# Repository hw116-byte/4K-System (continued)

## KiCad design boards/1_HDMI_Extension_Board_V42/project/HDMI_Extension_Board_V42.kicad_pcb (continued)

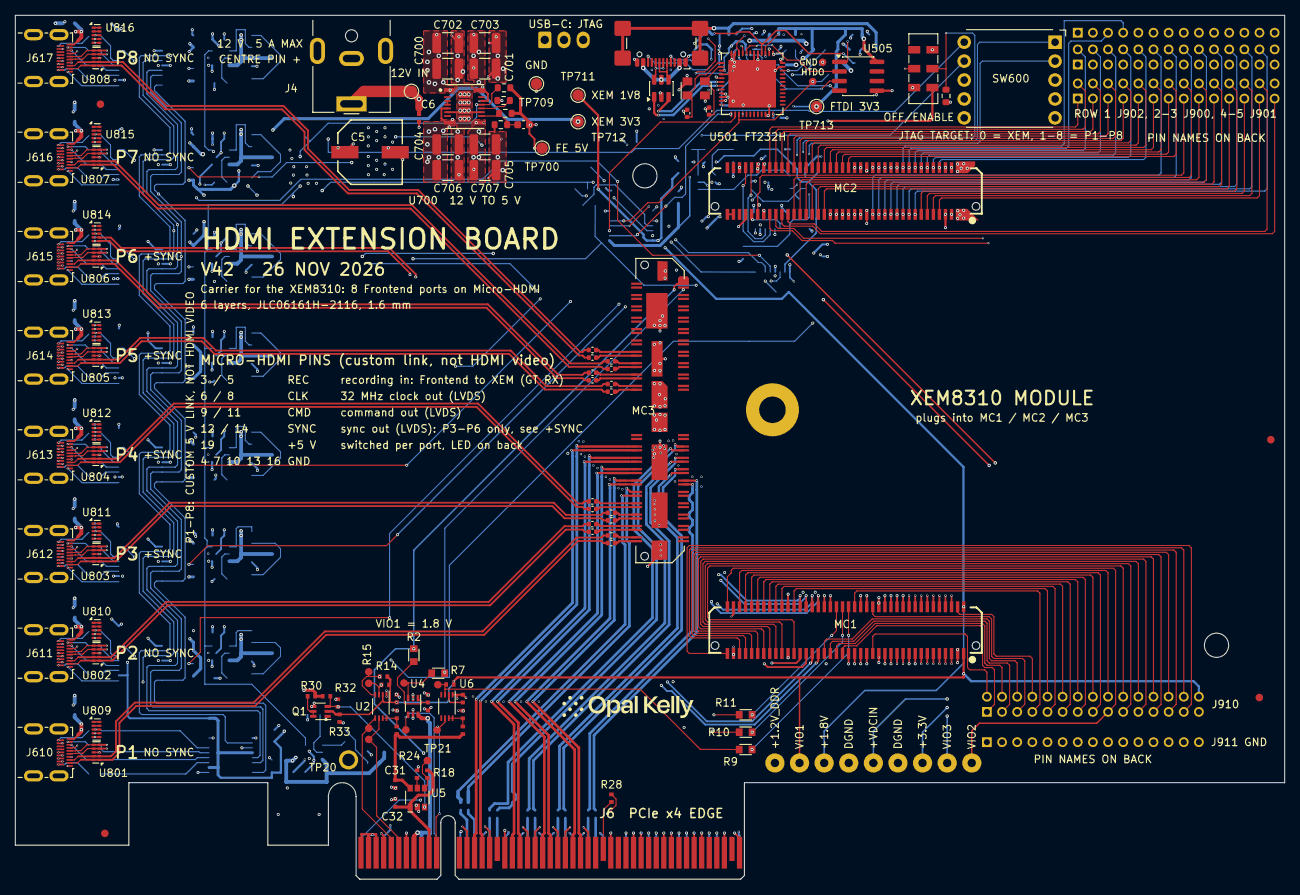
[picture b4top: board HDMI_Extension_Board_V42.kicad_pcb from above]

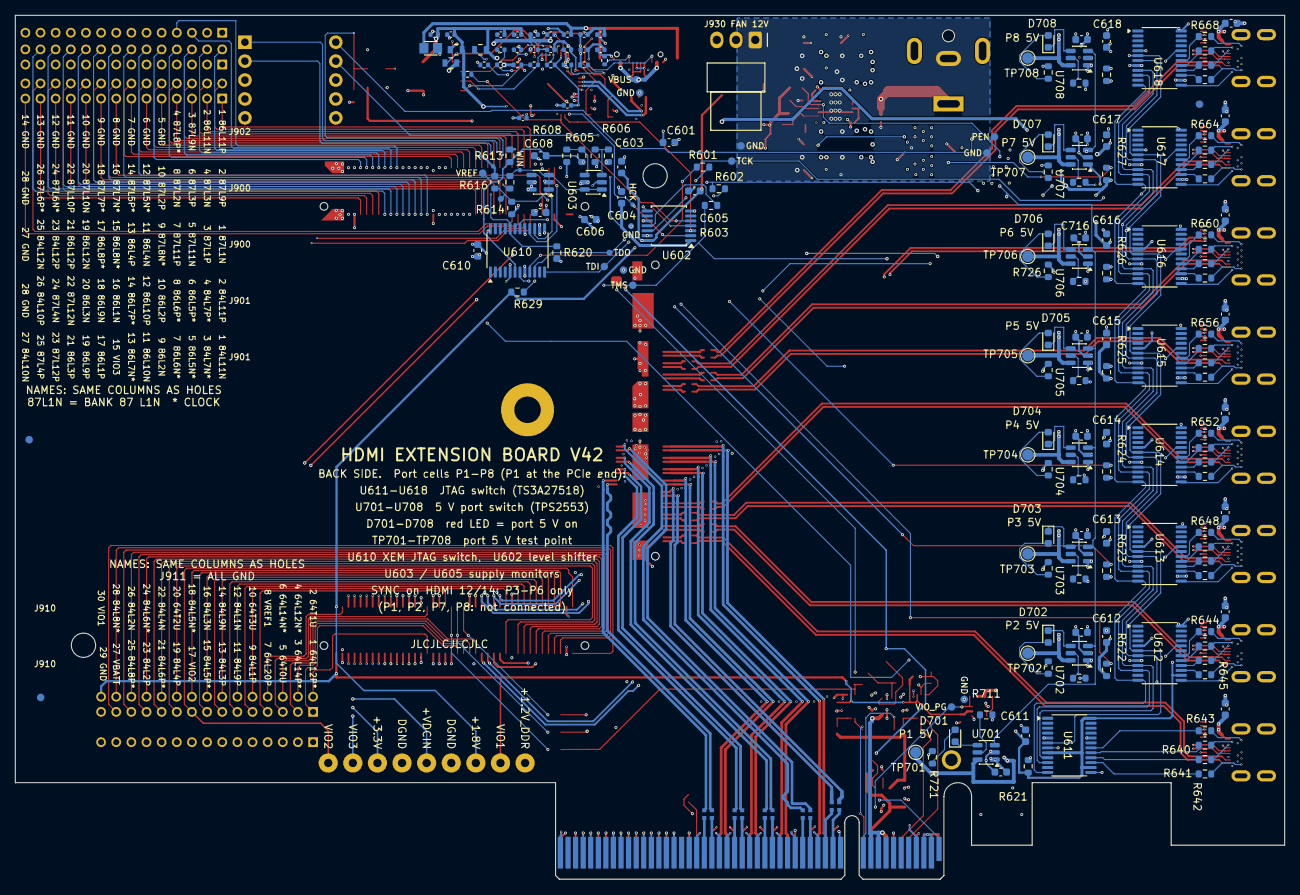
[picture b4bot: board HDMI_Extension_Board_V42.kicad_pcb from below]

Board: 6 copper layers, 167.6 x 114.1 mm, 340 parts (200 on the bottom side), 388 nets.

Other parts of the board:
*: Opal Kelly Logo; BRK_Logo_c689e08d
FID1, FID5, FID6, FID7: FIDUCIAL; BRK_FID1
FID2: FIDUCIAL; BRK_FID2
FID3: FIDUCIAL; BRK_FID3
FID4: FIDUCIAL; BRK_FID4
MH2, MH3: Standoff M3; Standoff_Hole_3.2mm_NPTH

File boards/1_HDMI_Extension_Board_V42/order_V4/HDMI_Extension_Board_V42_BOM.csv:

Comment,Designator,Footprint,JLCPCB Part #
CL05B104KO5NNNC (100nF 10% 16V X7R 0402),"C7,C8,C9,C10,C11,C12,C27,C28,C31,C32,C501,C502,C505,C508,C509,C510,C511,C514,C516,C517,C518",BRK8310_C10,C1525
CL05B224KO5NNNC (220nF 10% 16V X7R 0402),"C13,C14,C15,C16,C17,C18,C19,C20",BRK8310_C13,C16772
EEE-FK1E221GP,C5,BRK_C5,C401715
4.7u,C500,C500,C342983
18p,"C503,C504",C504,C22442494
100n,C506,C506,C1525
4.7u,"C507,C512,C513,C515",C515,C87147
10n,C519,C519,C2649513
CL05B104KB54PNC (100nF 10% 50V X7R 0402),C6,BRK_C6,C307331
2.2u,"C601,C603",C_0603_1608Metric,C100082
100nF,"C604,C605,C606,C609,C610,C611,C612,C613,C614,C615,C616,C617,C618,C711,C712,C713,C714,C715,C716,C717,C718",C_0603_1608Metric,C14663
1n,C608,C_0603_1608Metric,C8808
10uF,"C700,C701,C702,C703",C_1210_3225Metric,C77102
47uF,"C704,C705,C706,C707",C_1210_3225Metric,C77101
22pF,C708,C_0603_1608Metric,C376775
USBLC6-2SC6,D500,D500,C7519
RED,"D701,D702,D703,D704,D705,D706,D707,D708",LED_0603_1608Metric,C94869
600R,"FB500,FB501,FB502",FB502,C19330
220R @100MHz,FB503,FB503,C76818
PJ-063AH,J4,BarrelJack_CUI_PJ-063AH_Horizontal,C22434582
USB4110-GF-A,J500,J500,C5143397
467651001,"J610,J611,J612,J613,J614,J615,J616,J617",HDMI_Micro-D_Molex_46765-1xxx,C563878
YXY-PZ2.0-2X14PIN-DIP,"J900,J901",PinHeader_2x14_P2.00mm_V41,C56596886
YXY-PZ2.0-1X14PIN-DIP,J902,PinHeader_1x14_P2.00mm_V41,C56596719
YXY-PZ2.0-2X15PIN-DIP,J910,PinHeader_2x15_P2.00mm_V41,C56596887
YXY-PZ2.0-1X15PIN-DIP,J911,PinHeader_1x15_P2.00mm_V41,C56596720
PZ254V-11-01P,"J920,J921,J922,J923,J924,J925,J926,J927,J928",PinHeader_1x01_P2.54mm_Pad2.54_D1.1_V41,C492400
22-05-3031,J930,Molex_KK-254_22-05-3031_1x03_P2.54mm_Horizontal,C505040
BTE-040-01-F-D-A,"MC1,MC2",BRK_MC1,C2914307
QTH-040-01-F-D-DP-A,MC3,BRK_MC3,C7330812
SI1922EDH-T1-GE3,Q1,BRK8310_Q1,C141538
CRCW06030000Z0EA,"R2,R7,R9,R10,R11",BRK8310_R10,C844915
CRCW0402200KFKED,"R13,R23",BRK8310_R13,C482093
CRCW04024K75FKED,"R14,R15,R30,R31",BRK8310_R14,C844510
CRCW0402100KFKED,"R18,R24,R25,R32,R33,R502,R503",BRK8310_R18,C481918
CRCW04020000Z0ED,R28,BRK8310_R28,C190119
5.1k 1%,"R500,R501",R501,C2076825
2k,R504,R504,C482125
10k,"R505,R506,R509",R509,C71617
12k 1%,R507,R507,C481938
3.3k,"R600,R721,R722,R723,R724,R725,R726,R727,R728",R_0603_1608Metric,C22978
22R,"R601,R602,R603",R_0603_1608Metric,C23345
301k,R605,R_0603_1608Metric,C23026
100k,"R606,R608,R616",R_0603_1608Metric,C25803
402k,R607,R_0603_1608Metric,C23048
68k,R613,R_0603_1608Metric,C23231
4.7k,R614,R_0603_1608Metric,C23162
12k,R615,R_0603_1608Metric,C22790
10k,"R620,R621,R622,R623,R624,R625,R626,R627,R628",R_0603_1608Metric,C25804
1k,R629,R_0603_1608Metric,C21190
100R,"R640,R641,R642,R643,R644,R645,R646,R647,R648,R649,R650,R651,R652,R653,R654,R655,R656,R657,R658,R659,R660,R661,R662,R663,R664,R665,R666,R667,R668,R669,R670,R671",R_0603_1608Metric,C22775
40.2k,R700,R_0603_1608Metric,C137723
10k,"R701,R703",R_0603_1608Metric,C98220
13k,R702,R_0603_1608Metric,C22797
37.4k,"R711,R712,R713,R714,R715,R716,R717,R718",R_0603_1608Metric,C227846
SRBQ490100,SW600,ALPS_SRBQ490100_1P9T,C370985
JS202011JCQN,SW601,SW700,C221665
PCA9306DCUR,"U2,U6",BRK8310_U2,C33196
SN74AXC1T45DCK,U4,BRK8310_U4,C2677392
AP22653AW6-7,U5,BRK8310_U5,C1511768
FT232HQ-REEL,U501,U501,C82158
93LC56BT-I/SN,U505,SOIC-8_3.9x4.9mm_P1.27mm,C6164
TXU0304PWR,U602,TSSOP-14_4.4x5mm_P0.65mm,C4364118
TPS3700DDCR,U603,SOT-23-6,C33002
TPS3808G30DBVR,U605,SOT-23-6,C189211
TS3A27518EPWR,"U610,U611,U612,U613,U614,U615,U616,U617,U618",TSSOP-24_4.4x7.8mm_P0.65mm,C443721
TPSM63606RDLR,U700,TI_TPSM63606_RDL0020A_EVM,C5219325
TPS2553DBVR,"U701,U702,U703,U704,U705,U706,U707,U708",SOT-23-6,C55266
TPD4E02B04DQAR,"U801,U802,U803,U804,U805,U806,U807,U808,U809,U810,U811,U812,U813,U814,U815,U816",USON-10_2.5x1.0mm_P0.5mm,C106794
7U12000E18UCG 12MHz,Y500,Y500,C524717
CL10A105KB8NNNC (1uF 10% 50V X5R 0603),"C721,C722,C723,C724,C725,C726,C727,C728",C_0603_1608Metric,C15849
CL05B104KO5NNNC (100nF 10% 16V X7R 0402),"C745,C746,C747,C748,C749,C750,C751,C752,C753,C754,C755,C756,C757,C758,C759,C760",C_0402_1005Metric,C1525

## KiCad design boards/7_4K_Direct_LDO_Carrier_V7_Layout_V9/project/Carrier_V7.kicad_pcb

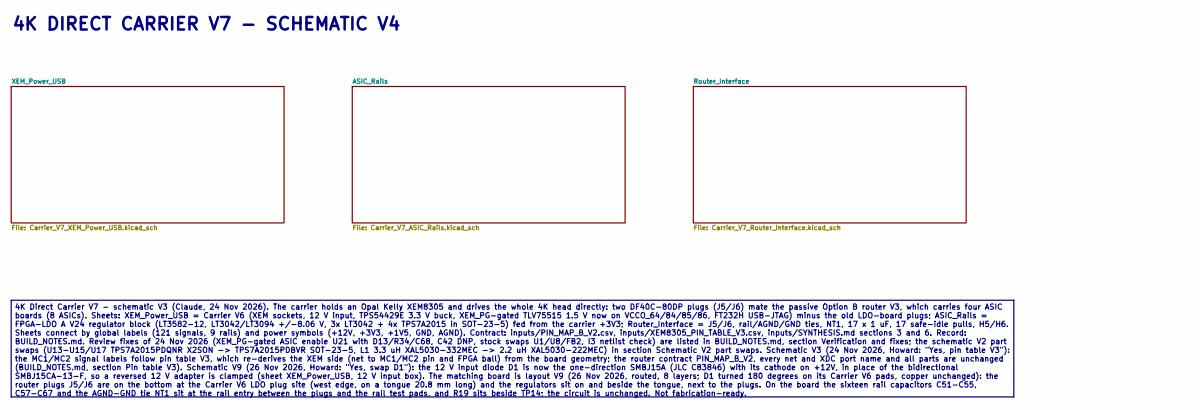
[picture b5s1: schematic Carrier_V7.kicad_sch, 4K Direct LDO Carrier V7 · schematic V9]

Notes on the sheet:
4K Direct Carrier V7 - schematic V3 (Claude, 24 Nov 2026). The carrier holds an Opal Kelly XEM8305 and drives the whole 4K head directly: two DF40C-80DP plugs (J5/J6) mate the passive Option B router V3, which carries four ASIC boards (8 ASICs). Sheets: XEM_Power_USB = Carrier V6 (XEM sockets, 12 V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
4K DIRECT CARRIER V7 - SCHEMATIC V4

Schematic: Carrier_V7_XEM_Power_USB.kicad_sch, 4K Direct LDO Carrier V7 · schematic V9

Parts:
C1: 0.1u 25v; C_0402_1005Metric; Voltage 25V; Tolerance 10%; MPN CL05B104KA5NNNC; LCSC C155422
C2: 220u 25v; CP_Panasonic_EEEFTE221XAL_D6.3x7.7_V3; MPN EEEFTE221XAL; LCSC C1881633
C3: 22u 35V; C_1206_3216Metric; Voltage 35V; Tolerance 20%; MPN C3216X5R1V226MTJ00E; LCSC C342620
C4: 0.1u 25V; C_0402_1005Metric; Voltage 25V; Tolerance 10%; MPN CL05B104KA5NNNC; LCSC C155422
C5: 1u 25V; C_0603_1608Metric; Voltage 25V; Tolerance 10%; MPN CL10A105KA8NNNC; LCSC C5673
C6: 3.3n 50V; C_0402_1005Metric; Voltage 50V; Tolerance 10%; MPN CL05B332KB5NNNC; LCSC C26404
C7: 0.1u 16V; C_0402_1005Metric; Voltage 16V; Tolerance 10%; MPN CL05B104KO5NNNC; LCSC C1525
C8, C9: 22u 10V; C_1206_3216Metric; Voltage 10V; Tolerance 10%; MPN CL31B226KPHNNNE; LCSC C87996
C10: 10p 50V; C_0402_1005Metric; Voltage 50V; Tolerance 5%; MPN CL05C100JB5NNNC; LCSC C32949
C11, C12: 4.7u 10V X5R; C_0402_1005Metric; MPN CL05A475MP5NRNC; LCSC C23733
C13: 4.7u; C_0402_1005Metric; Voltage 10V; MPN CL05A475MP5NRNC; LCSC C23733
C14, C16, C19, C22, C23, C24, C25, C28, C30, C31, C32, C34, C35, C36, C37, C38, C39, C40, C41, C70: 100n; C_0402_1005Metric; Voltage 16V; Tolerance 10%; MPN CL05B104KO5NNNC; LCSC C1525
C17, C18: 18p; C_0402_1005Metric; MPN C0402C180J5GACTU; LCSC C22442494
C20, C33: 10n; C_0402_1005Metric; Voltage 16V; Tolerance 10%; MPN C0402C103K4RACTU; LCSC C2649513
C21, C26, C27, C29: 4.7u; C_0402_1005Metric; Voltage 6.3V; Tolerance 20%; MPN JMK105BBJ475MV-F; LCSC C87147
C69: 4.7u; C_0402_1005Metric; MPN CL05A475MP5NRNC; LCSC C23733
D1: SMBJ15A; D_SMB; MPN SMBJ15A; LCSC C83846
D2: 598-8070-107F; LED_0603_1608Metric; MPN 5988070107F; LCSC C6695603
D3: APT1608LZGCK; LED_Kingbright_APT1608LZGCK_V2; Voltage 2.65V typ @2mA; MPN APT1608LZGCK; LCSC C5246833
D4: APT1608LSYCK/J3-PRV; LED_Kingbright_APT1608LSYCK_J3_PRV_V2; Voltage 1.85V typ @2mA; MPN APT1608LSYCK/J3-PRV; LCSC C5246836
FB1, FB3, FB4: 600R; Ferrite_Bead_Murata_BLM18KG601SN1D_0603_V4; MPN BLM18KG601SN1D; LCSC C85833
FB2: 220R @100MHz; BRK8305_A03_FB503; MANUFACTURER_PN BLM21PG221SH1D; LCSC C88994
H1, H2, H3, H4: XEM M3 NPTH; MountingHole_3.2mm_XEM_M3_Keepout
J3: PJ-102AH; PJ102AH; MPN PJ-102AH; LCSC C3096093
J4: USB4110-GF-A; USB_C_Receptacle_GCT_USB4110_GF_A_Horizontal; MANUFACTURER_PN USB4110-GF-A; LCSC C5143397
L1: 2.2uH; L_Coilcraft_XAL5030-332MEC; MPN XAL5030-222MEC; LCSC C920280
MC1: ERF6-50-03.5-L-DV-A-K-TR; MPN ERF6-50-03.5-L-DV-A-K-TR; LCSC C3642350
MC2: XEM_MC2_80; ERF6-40-03.5-L-DV-A-K-TR; MPN ERF6-40-03.5-L-DV-A-K-TR; LCSC C3652484
MC3: XEM_MC3_80; ERF6-40-03.5-L-DV-A-K-TR; MPN ERF6-40-03.5-L-DV-A-K-TR; LCSC C3652484
R1: 2.0k; R_0603_1608Metric; MPN CRCW06032K00FKEAHP; LCSC C313719
R2: 10k 1%; R_0402_1005Metric; MPN CRCW040210K0FKED; LCSC C71617
R3: 73.2k 1%; R_0402_1005Metric; MPN RC0402FR-0773K2L; LCSC C185398
R4: 22.1k 1%; R_0402_1005Metric; MPN RC0402FR-0722K1L; LCSC C163478
R5: 100k; R_0402_1005Metric; MPN ERJ2RKF1003X; LCSC C192169
R6, R7: 5.1k 1%; R_0402_1005Metric; MPN CRCW04025K10FKEDC; LCSC C2076825
R8, R9: 100k; R_0402_1005Metric; Tolerance 1%; MPN CRCW0402100KFKED; LCSC C481918
R10: 2k; R_0402_1005Metric; Tolerance 1%; MPN CRCW04022K00FKED; LCSC C482125
R11, R12: 10k; R_0402_1005Metric; Tolerance 1%; MPN CRCW040210K0FKED; LCSC C71617
R13: 12k 1%; R_0402_1005Metric; Tolerance 1%; MPN CRCW040212K0FKED; LCSC C481938
R14: 3.0k 1%; R_0603_1608Metric; Rating 0603 1% 0.1W minimum; MPN CRCW06033K00FKEA; LCSC C844780
R15: 6.8k 1%; R_0603_1608Metric; Rating 0603 1% 0.1W minimum; MPN CRCW06036K80FKEA; LCSC C844805
TP1: 12V; TestPoint_Pad_D1.5mm
TP2: 3V3_MAIN; TestPoint_Pad_D1.5mm
TP3: 1V5; TestPoint_Pad_D1.5mm
TP4: XEM_1V8; TestPoint_Pad_D1.5mm
TP5: USB_5V; TestPoint_Pad_D1.5mm
TP6: USB_3V3; TestPoint_Pad_D1.5mm
TP7: GND_PWR; TestPoint_Pad_D1.5mm
TP8: GND_USB; TestPoint_Pad_D1.5mm
U1: TPS54429ERSAT; TPS54429E_RSA; MPN TPS54429ERSAT; LCSC C1880068
U2: TLV75515PDRVR; Texas_WSON-6_2x2mm_P0.65mm_EP1x1.6mm_TLV755_DRV_V2; MPN TLV75515PDRVR; LCSC C2868685
U3: FT232HQ; BRK8305_A03_U501; MANUFACTURER_PN FT232HQ-REEL; LCSC C82158
U4, U5, U6, U7: SN74AXC1T45DBVR; BRK8305_A03_U500; MANUFACTURER_PN SN74AXC1T45DBVR; LCSC C2677376
U8: 93AA56B-I/MS; BRK8305_A03_U505; MANUFACTURER_PN 93AA56B-I/MS; LCSC C1350563
Y1: 12MHz; BRK8305_A03_Y500; MPN ABM8-12.000MHZ-B2-T; LCSC C596894

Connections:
+1V5: C11.1, C69.1, C70.1, MC1.1 (VCCO_84), MC1.2 (VCCO_64), MC1.3 (VCCO_84), MC1.4 (VCCO_64), MC2.37 (VCCO_85), MC2.39 (VCCO_85), MC2.41 (VCCO_86), MC2.43 (VCCO_86), TP3.1, U2.1 (OUT)
+3V3: C8.1, C9.1, C10.1, C12.1, L1.2, R3.1, R14.1, TP2.1, U1.16 (VO), U2.6 (IN); also elsewhere on the board
+12V: C1.1, C2.1, C3.1, C4.1, D1.1 (K), J3.1, MC1.91 (VDCIN), MC1.93 (VDCIN), MC1.95 (VDCIN), MC1.97 (VDCIN), MC1.99 (VDCIN), R1.1, R2.1, TP1.1, U1.13 (VIN1), U1.14 (VIN2), U1.15 (VIN3)
/XEM_Power_USB/FB_BUCK: C10.2, R3.2, R4.1, U1.1 (VFB)
/XEM_Power_USB/USBJTAG_1.8V_ANALOG: C32.2, U3.37 (VCCA)
/XEM_Power_USB/USBJTAG_1.8V_CORE: C31.2, U3.38 (VCORE)
/XEM_Power_USB/USBJTAG_3.3V: C19.1, C21.1, C22.1, C23.1, C24.1, C25.1, C26.1, C34.1, C36.1, C38.1, C40.1, FB3.1, FB4.1, R9.1, R11.2, R12.1, TP6.1, U3.12 (VCCIO), U3.24 (VCCIO), U3.39 (VCCD), U3.46 (VCCIO), U4.1 (Vcca), U4.5 (DIR), U5.1 (Vcca), U5.5 (DIR), U6.1 (Vcca), U7.1 (Vcca), U7.5 (DIR), U8.8 (VCC)
/XEM_Power_USB/USBJTAG_3.3V_PHY: C29.1, C30.1, FB4.2, U3.3 (VPHY)
/XEM_Power_USB/USBJTAG_3.3V_PLL: C27.1, C28.1, FB3.2, U3.8 (VPLL)
/XEM_Power_USB/USBJTAG_5V_FILTERED: C13.1, C14.1, FB1.2, U3.40 (VREGIN)
/XEM_Power_USB/USBJTAG_EECLK: R9.2, U3.44 (EECLK), U8.2 (CLK)
/XEM_Power_USB/USBJTAG_EECS: R8.1, U3.45 (EECS), U8.1 (CS)
/XEM_Power_USB/USBJTAG_EEDATA: R10.1, U3.43 (EEDATA), U8.3 (DI)
/XEM_Power_USB/XEM_1.8V: C35.1, C37.1, C39.1, C41.1, MC2.75 (1V8_OUT), MC2.77 (1V8_OUT), MC2.79 (1V8_OUT), TP4.1, U4.6 (Vccb), U5.6 (Vccb), U6.6 (Vccb), U7.6 (Vccb)
ASIC1_CLK32MHz_Out: MC2.26 (B85_L8P_HDGC); also elsewhere on the board
ASIC1_DATA1: MC2.11 (B85_L1P); also elsewhere on the board
ASIC1_DATA2: MC2.13 (B85_L1N); also elsewhere on the board
ASIC1_DATA3: MC2.15 (B85_L2P); also elsewhere on the board
ASIC1_DATA4: MC2.17 (B85_L2N); also elsewhere on the board
ASIC1_DATA5: MC2.28 (B85_L8N_HDGC); also elsewhere on the board
ASIC1_DATA6: MC2.29 (B85_L5N_HDGC); also elsewhere on the board
ASIC1_DATA7: MC2.30 (B85_L9P); also elsewhere on the board
ASIC1_DATA8: MC2.36 (B85_L10N); also elsewhere on the board
ASIC1_READ: MC2.38 (B85_L11P); also elsewhere on the board
ASIC1_SYNC: MC2.25 (B85_L4N); also elsewhere on the board
ASIC2_CLK32MHz_Out: MC2.64 (B86_L8P_HDGC); also elsewhere on the board
ASIC2_DATA1: MC2.55 (B86_L5N_HDGC); also elsewhere on the board
ASIC2_DATA2: MC2.56 (B86_L10P); also elsewhere on the board
ASIC2_DATA3: MC2.58 (B86_L10N); also elsewhere on the board
ASIC2_DATA4: MC2.57 (B86_L4P); also elsewhere on the board
ASIC2_DATA5: MC2.66 (B86_L8N_HDGC); also elsewhere on the board
ASIC2_DATA6: MC2.68 (B86_L7P_HDGC); also elsewhere on the board
ASIC2_DATA7: MC2.67 (B86_L2N); also elsewhere on the board
ASIC2_DATA8: MC2.70 (B86_L7N_HDGC); also elsewhere on the board
ASIC2_READ: MC2.71 (B86_L1N); also elsewhere on the board
ASIC2_SYNC: MC2.63 (B86_L3N); also elsewhere on the board
ASIC3_4_TOP_SPI_CLK: MC1.17 (B84_L9P); also elsewhere on the board
ASIC3_4_TOP_SPI_LATCH: MC1.19 (B84_L9N); also elsewhere on the board
ASIC3_CLK32MHz_Out: MC2.31 (B85_L6P_HDGC); also elsewhere on the board
ASIC3_DATA1: MC2.21 (B85_L3N); also elsewhere on the board
ASIC3_DATA2: MC2.23 (B85_L4P); also elsewhere on the board
ASIC3_DATA3: MC2.24 (B85_L7N_HDGC); also elsewhere on the board
ASIC3_DATA4: MC2.27 (B85_L5P_HDGC); also elsewhere on the board
ASIC3_DATA5: MC2.34 (B85_L10P); also elsewhere on the board
ASIC3_DATA6: MC2.33 (B85_L6N_HDGC); also elsewhere on the board
ASIC3_DATA7: MC2.40 (B85_L11N); also elsewhere on the board
ASIC3_DATA8: MC2.42 (B85_L12P); also elsewhere on the board
ASIC3_READ: MC2.44 (B85_L12N); also elsewhere on the board
ASIC3_SPI_DL: MC1.21 (B84_L10P); also elsewhere on the board
ASIC3_SPI_DR: MC1.23 (B84_L10N); also elsewhere on the board
ASIC3_SYNC: MC2.32 (B85_L9N); also elsewhere on the board
ASIC4_CLK32MHz_Out: MC2.53 (B86_L5P_HDGC); also elsewhere on the board
ASIC4_DATA1: MC2.48 (B86_L12P); also elsewhere on the board
ASIC4_DATA2: MC2.50 (B86_L12N); also elsewhere on the board
ASIC4_DATA3: MC2.49 (B86_L6P_HDGC); also elsewhere on the board
ASIC4_DATA4: MC2.51 (B86_L6N_HDGC); also elsewhere on the board
ASIC4_DATA5: MC2.59 (B86_L4N); also elsewhere on the board
ASIC4_DATA6: MC2.61 (B86_L3P); also elsewhere on the board
ASIC4_DATA7: MC2.62 (B86_L9N); also elsewhere on the board
ASIC4_DATA8: MC2.65 (B86_L2P); also elsewhere on the board
ASIC4_READ: MC2.69 (B86_L1P); also elsewhere on the board
ASIC4_SPI_DL: MC2.52 (B86_L11P); also elsewhere on the board
ASIC4_SPI_DR: MC1.43 (B64_L22P); also elsewhere on the board
ASIC4_SYNC: MC2.54 (B86_L11N); also elsewhere on the board
ASIC5_CLK32MHz_Out: MC1.63 (B64_L12P_GC); also elsewhere on the board
ASIC5_DATA1: MC1.35 (B64_L24P); also elsewhere on the board
ASIC5_DATA2: MC1.36 (B64_L18P); also elsewhere on the board
ASIC5_DATA3: MC1.37 (B64_L24N); also elsewhere on the board
ASIC5_DATA4: MC1.38 (B64_L18N); also elsewhere on the board
ASIC5_DATA5: MC1.65 (B64_L12N_GC); also elsewhere on the board
ASIC5_DATA6: MC1.69 (B64_L11N_GC); also elsewhere on the board
ASIC5_DATA7: MC1.71 (B64_L10P); also elsewhere on the board
ASIC5_DATA8: MC1.72 (B64_L4P); also elsewhere on the board
ASIC5_READ: MC1.73 (B64_L10N); also elsewhere on the board
ASIC5_SYNC: MC1.59 (B64_T3U_N12); also elsewhere on the board
ASIC6_CLK32MHz_Out: MC1.67 (B64_L11P_GC); also elsewhere on the board
ASIC6_DATA1: MC1.74 (B64_L4N); also elsewhere on the board
ASIC6_DATA2: MC1.76 (B64_L3P); also elsewhere on the board
ASIC6_DATA3: MC1.77 (B64_L9N); also elsewhere on the board
ASIC6_DATA4: MC1.78 (B64_L3N); also elsewhere on the board
ASIC6_DATA5: MC1.82 (B64_L2N); also elsewhere on the board
ASIC6_DATA6: MC1.83 (B64_L7P); also elsewhere on the board
ASIC6_DATA7: MC1.84 (B64_L1P); also elsewhere on the board
ASIC6_DATA8: MC1.86 (B64_L1N); also elsewhere on the board
ASIC6_READ: MC1.85 (B64_L7N); also elsewhere on the board
ASIC6_SYNC: MC1.81 (B64_L8N); also elsewhere on the board
ASIC7_8_TOP_SPI_CLK: MC1.18 (B84_L3P); also elsewhere on the board
ASIC7_8_TOP_SPI_LATCH: MC1.20 (B84_L3N); also elsewhere on the board
ASIC7_CLK32MHz_Out: MC1.26 (B84_L5P_HDGC); also elsewhere on the board
ASIC7_DATA1: MC1.10 (B84_L1P); also elsewhere on the board
ASIC7_DATA2: MC1.12 (B84_L1N); also elsewhere on the board
ASIC7_DATA3: MC1.14 (B84_L2P); also elsewhere on the board
ASIC7_DATA4: MC1.16 (B84_L2N); also elsewhere on the board
ASIC7_DATA5: MC1.28 (B84_L5N_HDGC); also elsewhere on the board
ASIC7_DATA6: MC1.30 (B84_L6P_HDGC); also elsewhere on the board
ASIC7_DATA7: MC1.29 (B84_L12P); also elsewhere on the board
ASIC7_DATA8: MC1.31 (B84_L12N); also elsewhere on the board
ASIC7_READ: MC1.32 (B84_L6N_HDGC); also elsewhere on the board
ASIC7_SPI_DL: MC1.22 (B84_L4P); also elsewhere on the board
ASIC7_SPI_DR: MC1.24 (B84_L4N); also elsewhere on the board
ASIC7_SYNC: MC1.25 (B84_L11P); also elsewhere on the board
ASIC8_CLK32MHz_Out: MC1.56 (B64_L13P_GC); also elsewhere on the board
ASIC8_DATA1: MC1.42 (B64_L17N); also elsewhere on the board
ASIC8_DATA2: MC1.44 (B64_L16P); also elsewhere on the board
ASIC8_DATA3: MC1.46 (B64_L16N); also elsewhere on the board
ASIC8_DATA4: MC1.48 (B64_L15P); also elsewhere on the board
ASIC8_DATA5: MC1.60 (B64_T2U_N12); also elsewhere on the board
ASIC8_DATA6: MC1.64 (B64_L6P); also elsewhere on the board
ASIC8_DATA7: MC1.66 (B64_L6N); also elsewhere on the board
ASIC8_DATA8: MC1.68 (B64_L5P); also elsewhere on the board
ASIC8_READ: MC1.70 (B64_L5N); also elsewhere on the board
ASIC8_SPI_DL: MC1.50 (B64_L15N); also elsewhere on the board
ASIC8_SPI_DR: MC1.52 (B64_L14P_GC); also elsewhere on the board
ASIC8_SYNC: MC1.54 (B64_L14N_GC); also elsewhere on the board
BOARD1_CLK: MC1.75 (B64_L9P); also elsewhere on the board
BOARD1_SPI_CLK: MC1.9 (B84_L7P_HDGC); also elsewhere on the board
BOARD1_SPI_LATCH: MC1.11 (B84_L7N_HDGC); also elsewhere on the board
BOARD3_CLK: MC1.88 (B64_T1U_N12); also elsewhere on the board
BOARD3_SPI_CLK: MC1.41 (B64_L23N); also elsewhere on the board
BOARD3_SPI_LATCH: MC1.45 (B64_L22N); also elsewhere on the board
CHIP_RESET_SHARED: MC1.27 (B84_L11N); also elsewhere on the board
FE_RESET_SHARED: MC1.39 (B64_L23P); also elsewhere on the board
GND: C1.2, C2.2, C3.2, C4.2, C5.1, C6.1, C8.2, C9.2, C11.2, C12.2, C13.2, C14.2, C16.2, C17.2, C18.2, C19.2, C20.1, C21.2, C22.2, C23.2, C24.2, C25.2, C26.2, C27.2, C28.2, C29.2, C30.2, C31.1, C32.1, C33.2, C34.2, C35.2, C36.2, C37.2, C38.2, C39.2, C40.2, C41.2, C69.2, C70.2, D1.2 (A), D2.1 (K), D3.1 (K), D4.1 (K), FB2.1, J3.2, J4.A1 (GND), J4.A12 (GND), J4.B1 (GND), J4.B12 (GND), MC1.5 (DGND), MC1.6 (DGND), MC1.7 (DGND), MC1.8 (DGND), MC1.33 (DGND), MC1.34 (DGND), MC1.61 (DGND), MC1.62 (DGND), MC1.92 (DGND), MC1.94 (DGND), MC1.96 (DGND), MC1.98 (DGND), MC1.100 (DGND), MC2.6 (DGND), MC2.9 (DGND), MC2.20 (DGND), MC2.35 (DGND), MC2.45 (DGND), MC2.46 (DGND), MC2.47 (DGND), MC2.72 (DGND), MC2.73 (DGND), MC2.74 (DGND), MC2.76 (DGND), MC3.1 (DGND), MC3.2 (DGND), MC3.7 (DGND), MC3.8 (DGND), MC3.13 (DGND), MC3.14 (DGND), MC3.19 (DGND), MC3.20 (DGND), MC3.25 (DGND), MC3.26 (DGND), MC3.31 (DGND), MC3.32 (DGND), MC3.37 (DGND), MC3.38 (DGND), MC3.43 (DGND), MC3.44 (DGND), MC3.49 (DGND), MC3.50 (DGND), MC3.55 (DGND), MC3.56 (DGND), MC3.61 (DGND), MC3.62 (DGND), MC3.67 (DGND), MC3.68 (DGND), MC3.73 (DGND), MC3.74 (DGND), MC3.79 (DGND), MC3.80 (DGND), R4.2, R5.2, R6.1, R7.2, R8.2, R13.2, TP7.1, TP8.1, U1.4 (GND), U1.7 (PGND1), U1.8 (PGND2), U1.17 (EP/PGND), U2.3 (GND), U2.7 (EP), U3.4 (AGND), U3.9 (AGND), U3.10 (GND), U3.11 (GND), U3.22 (GND), U3.23 (GND), U3.35 (GND), U3.36 (GND), U3.41 (AGND), U3.42 (TEST), U3.47 (GND), U3.48 (GND), U3.PAD, U4.2 (GND), U5.2 (GND), U6.2 (GND), U6.5 (DIR), U7.2 (GND), U8.5 (VSS), Y1.2 (CASE), Y1.4 (CASE); also elsewhere on the board
IMP_TST_SHARED: MC1.40 (B64_L17P); also elsewhere on the board
JTAG_TCK_1.8V: MC2.1 (JTAG_TCK), U4.4 (B)
JTAG_TDI_1.8V: MC2.3 (JTAG_TDI), U5.4 (B)
JTAG_TDO_1.8V: MC2.7 (JTAG_TDO), U6.4 (B)
JTAG_TMS_1.8V: MC2.5 (JTAG_TMS), U7.4 (B)
unnamed: C16.1, FB2.2, J4.M1 (SHELL), J4.M2 (SHELL), J4.M3 (SHELL), J4.M4 (SHELL)
unnamed: D2.2 (A), R1.2
unnamed: D3.2 (A), R14.2
unnamed: D4.2 (A), R15.2
unnamed: J4.A5 (CC1), R6.2
unnamed: J4.B5 (CC2), R7.1
unnamed: MC2.14 (VREFP), MC2.16 (GNDADC)
unnamed: R2.2, U1.6 (EN)
unnamed: C6.2, U1.3 (SS)
unnamed: C7.2, L1.1, U1.9 (SW1), U1.10 (SW2), U1.11 (SW3)
unnamed: C7.1, U1.12 (VBST)
unnamed: C5.2, U1.2 (VREG5)
unnamed: U3.13 (ADBUS0_/_TCK_/_SK), U4.3 (A)
unnamed: U3.14 (ADBUS1_/_TDI_/_DO), U5.3 (A)
unnamed: U3.15 (ADBUS2_/_TDO_/_DI), U6.3 (A)
unnamed: U3.16 (ADBUS3_/_TMS_/_CS), U7.3 (A)
unnamed: C17.1, U3.1 (OSCI), Y1.1 (OSC1)
unnamed: C18.1, U3.2 (OSCO), Y1.3 (OSC2)
unnamed: R13.1, U3.5 (REF)
unnamed: C33.1, R12.2, U3.34 (~RESET)
unnamed: R10.2, R11.1, U8.4 (DO)
STIM_CHB_SHARED: MC1.57 (B64_L19N); also elsewhere on the board
STIM_CHIP1_SPI_DL: MC1.13 (B84_L8P_HDGC); also elsewhere on the board
STIM_CHIP1_SPI_DR: MC1.15 (B84_L8N_HDGC); also elsewhere on the board
STIM_CHIP2_SPI_DL: MC1.51 (B64_L20P); also elsewhere on the board
STIM_CHIP2_SPI_DR: MC1.53 (B64_L20N); also elsewhere on the board
STIM_CHIP3_SPI_DL: MC1.47 (B64_L21P); also elsewhere on the board
STIM_CHIP3_SPI_DR: MC1.49 (B64_L21N); also elsewhere on the board
STIM_CHIP4_SPI_DL: MC1.79 (B64_L8P); also elsewhere on the board
STIM_CHIP4_SPI_DR: MC1.80 (B64_L2P); also elsewhere on the board
STIM_CLK_SHARED: MC1.55 (B64_L19P); also elsewhere on the board
STIM_EN_SHARED: MC1.58 (B64_L13N_GC); also elsewhere on the board
STIM_START_SHARED: MC2.60 (B86_L9P); also elsewhere on the board
USBJTAG_5V_IN: C20.2, FB1.1, J4.A4 (VBUS), J4.A9 (VBUS), J4.B4 (VBUS), J4.B9 (VBUS), R15.1, TP5.1
USB_D_N: J4.A7 (DN1), J4.B7 (DN2), U3.6 (DM)
USB_D_P: J4.A6 (DP1), J4.B6 (DP2), U3.7 (DP)
XEM PG: MC1.90 (XEM8305_PG), R5.1, U2.4 (EN); also elsewhere on the board

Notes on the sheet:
Vin_12V
Function: U7 translates TMS from FTDI3.3V to XEM1.8V. Source / changes: Opal Kelly BRK8305 A03,25Oct2023, JTAG sheet8/PDFp4: U504/C525/C526 -> U7/C40/C41. https://pins.opalkelly.com/downloads/583/download?category_id=3 Same SN74AXC1T45DBVR and two100nF values; topology unchanged. Codex redraw follo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
Function: U5 translates TDI from FTDI3.3V to XEM1.8V. Source / changes: Opal Kelly BRK8305 A03,25Oct2023, JTAG sheet8/PDFp4: U502/C515/C516 -> U5/C36/C37. https://pins.opalkelly.com/downloads/583/download?category_id=3 Same SN74AXC1T45DBVR and two100nF values; topology unchanged. Codex redraw follo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
Function: U1 converts 12 V to the main carrier 3.3 V rail. R3/R4/C10 form its feedback network. TP2 probes 3.3 V after L1; TP3 probes 1.5 V. D3/R14 indicate voltage presence (about 0.3 mA nominal), not power-good status. U2 derives 1.5 V from 3.3 V when enabled by XEM_PG. Source / changes: Inherite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
VBuck_3.3V
Function: J4 is a horizontal USB2 device socket; cable entry is parallel to the PCB. R6/R7 are CC pulldowns; C16/FB2 connect shield to GND at high frequency. Source / changes: GCT USB4110-GF-A, USB4110 revB4,22May2024,sheet1/2: https://gct.co/files/drawings/usb4110.pdf Codex adapts BRK8305 A03,25Oc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
Function: U6 translates TDO from XEM1.8V to FTDI3.3V. Source / changes: Opal Kelly BRK8305 A03,25Oct2023, JTAG sheet8/PDFp4: U503/C519/C520 -> U6/C38/C39. https://pins.opalkelly.com/downloads/583/download?category_id=3 Same SN74AXC1T45DBVR and two100nF values; topology unchanged. Codex redraw follo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
Level shifters (BRK8305 style)
Function: J3 receives barrel-jack12V. C2 stores input charge; C1 bypasses XEM12V. D1 shunts transients and clamps a reversed adapter. R1/D2 indicate input voltage; TP1/TP7 provide12V/GND probe access. Source / changes: Inherited carrier input structure; original author/reference is not established.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
Function: D4 shows rawUSB5V; R15=6.8kohm retains about0.47mA typical LED load. TP5=rawUSB5V; TP6=FTDI3.3V; TP8=GND. Source / changes: Codex probe/LED branch; V2 APT1608LSYCK/J3-PRV replaces AA1608LSYSK. R15 value and all electrical connections retained. Kingbright DSAN8389,V5B,6Jan2021,p1land/ pola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
XEM8305 sockets MC1-MC3 + XEM 1.8 V (V7: 121 router lines on banks 64/84/85/86, VCCO 1.5 V on all four)
Function: H1-H4 align carrier mounting holes to XEM8305. Source / changes: Opal Kelly XEM8305-AXX Mechanical Drawing, PCB Revision AXX,sheet1, and XEM8305 Mating Board Diagram, sheet1; dimensionsmm. https://docs.opalkelly.com/xem8305/specifications/ Codex registration Xcarrier=101+Ymodule,Ycarrier=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
Function: U4 translates TCK from FTDI3.3V to XEM1.8V. Source / changes: Opal Kelly BRK8305 A03,25Oct2023, JTAG sheet8/PDFp4: U500/C503/C504 -> U4/C34/C35. https://pins.opalkelly.com/downloads/583/download?category_id=3 Same SN74AXC1T45DBVR and two100nF values; topology unchanged. Codex redraw follo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
Function: TP4 probes the module-sourced1.8V translator supply. Source / changes: Codex adds one passive pad at C35 rail. Opal Kelly XEM8305 Expansion Connectors /1.8V Power Supply: https://docs.opalkelly.com/xem8305/expansion-connectors/ No LED/load added to this rail or FTDI internal1.8V nodes.
Function: U3 converts USB2 to JTAG through its MPSSE engine. Y1 is its12MHz reference; U8 stores optional USB identity/configuration. Local capacitors bypass each supply; FB1/FB3/FB4 separate the shown rail branches. Source / changes: inherited Opal Kelly BRK8305 A03,25Oct2023,JTAG sheet8/ PDFp4; l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
Function: Short MC2.14 (VREFP) to MC2.16 (GNDADC) to select the XEM8305 internal SYSMON ADC reference. Source / changes: Opal Kelly XEM8305, Expansion Connectors, SYSMON; web page accessed 31 Oct 2026: https://docs.opalkelly.com/xem8305/expansion-connectors/ Codex V6 adds direct copper instead of a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
1. Function: MC1 (banks 64, 84) and MC2 (banks 85, 86) carry the 121 LVCMOS15 lines of the 4K head to the router plugs J5/J6 (sheet Router_Interface) by global labels: 88 ASIC outputs into the FPGA (DATA1-8, READ, SYNC and CLK32MHz_Out of ASIC1-8) and 33 FPGA outputs (BOARD1/3 clocks, SPI clocks, l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
